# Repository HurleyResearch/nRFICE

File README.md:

# nRFICE
### nRF5340 with ICE40UP5K including JLink OB for instant BLE and FPGA development with zero dongles
In order to develop a number of comercial products, we (here at Hurley Research in Santa Cruz CA) needed a simple bluetooth 5 plus FPGA platform. nRFICE is meant to be a maximally simple solution for launching projects that require MCU plus FPGA and certainly if Bluetooth including mesh is needed.
### Arduino Uno compatibility
nRFICE is physically compatible with Arduino Uno shields, but take care that the GPIO level is 3.3V.
### JLink OB
Comercial eval/dev boards from chip manufactures, such as Nordic Semi, typically have the JLink debugger hardware embedded on the board for convenience. We have included JLink OB on nRFICE, allowing developers to get started without any additional hardare, programming dongles, etc. Out of box demos for both nRF5340 and ICE40UP5K can be loaded and debugged immediately with a single usb cable, or over BLE with the nRFICE android app.

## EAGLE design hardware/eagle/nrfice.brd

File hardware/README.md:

# nRFICE Hardware
Everything about the nRFICE PCB
- Eagle design files
- Gerbers
- Schematic
- Bill of matrials
- Pinout diagram

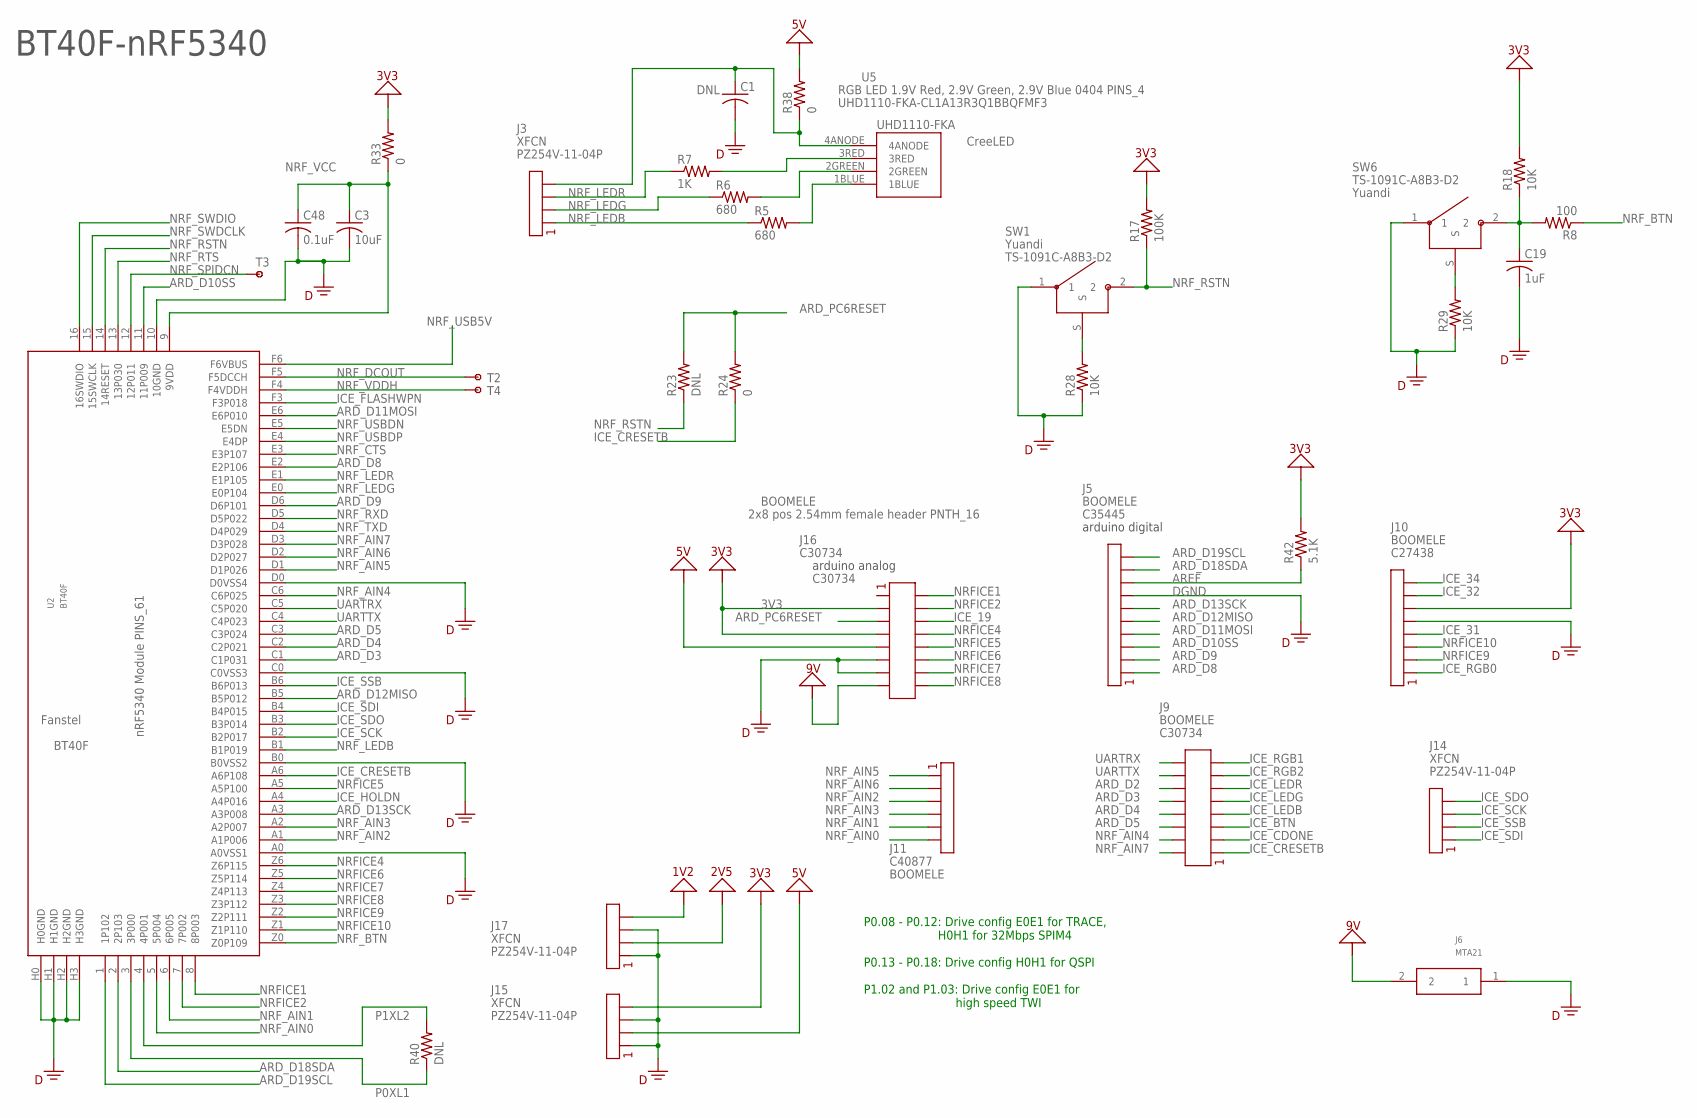
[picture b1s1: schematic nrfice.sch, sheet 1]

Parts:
C1: DNL; RCL_C0402; MPN CL05A105KP5NNNC
C3: 10uF; RCL_C0805; MPN CL21A106KOQNNNE
C19: 1uF; RCL_C0402; MPN CL05A105KP5NNNC
C48: 0.1uF; RCL_C0402; MPN C0402C104K8RAC7867
J3, J14, J15, J17: PZ254V-11-04P; MPN PZ254V-11-04P
J5: C35445; MPN C35445
J6: MTA21
J9, J16: C30734; MPN C30734
J10: C27438; MPN C27438
J11: C40877; MPN C40877
R5, R6: 680; RCL_R0402; MPN RC0402FR-07680RL
R7: 1K; RCL_R0402; MPN RC0402FR-071KL
R8: 100; RCL_R0402; MPN RC0402FR-07100RL
R17: 100K; RCL_R0402; MPN RC0402FR-07100KL
R18, R28, R29: 10K; RCL_R0402; MPN RC0402FR-0710KL
R23, R40: DNL; RCL_R0402; MPN RC0402FR-0710KL
R24, R38: 0; RCL_R0402; MPN RC0402FR-070RL
R33: 0; RCL_R0603; MPN RC0603FR-070RL
R42: 5.1K; RCL_R0402; MPN RC0402FR-075K1L
SW1, SW6: TS-1091C-A8B3-D2; MPN TS-1091C-A8B3-D2
T2, T3, T4: MTA1
U2: BT40F; MPN BT40F
U5: UHD1110-FKA; MPN UHD1110-FKA-CL1A13R3Q1BBQFMF3

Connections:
1V2: J17.4; also elsewhere on the board
2V5: J17.2; also elsewhere on the board
3V3: J10.6, J15.4, J16.3, J16.7, R17.2, R18.2, R33.2, R42.2; also elsewhere on the board
5V: J15.2, J16.9, R38.2; also elsewhere on the board
9V: J6.2, J16.15; also elsewhere on the board
ARD_D2: J9.12; also elsewhere on the board
ARD_D3: J9.10, U2.C1 (C1P031); also elsewhere on the board
ARD_D4: J9.8, U2.C2 (C2P021); also elsewhere on the board
ARD_D5: J9.6, U2.C3 (C3P024); also elsewhere on the board
ARD_D8: J5.1, U2.E2 (E2P106); also elsewhere on the board
ARD_D9: J5.2, U2.D6 (D6P101); also elsewhere on the board
ARD_D10SS: J5.3, U2.11 (11P009); also elsewhere on the board
ARD_D11MOSI: J5.4, U2.E6 (E6P010); also elsewhere on the board
ARD_D12MISO: J5.5, U2.B5 (B5P012); also elsewhere on the board
ARD_D13SCK: J5.6, U2.A3 (A3P008); also elsewhere on the board
ARD_D18SDA: J5.9, U2.2 (2P103); also elsewhere on the board
ARD_D19SCL: J5.10, U2.1 (1P102); also elsewhere on the board
ARD_PC6RESET: J16.5, R23.2, R24.2
AREF: J5.8, R42.1
DGND: C1.2, C3.2, C19.2, C48.2, J5.7, J6.1, J10.5, J15.1, J15.3, J16.11, J16.13, J17.1, J17.3, R28.1, R29.1, SW1.1, SW6.1, U2.10 (10GND), U2.A0 (A0VSS1), U2.B0 (B0VSS2), U2.C0 (C0VSS3), U2.D0 (D0VSS4), U2.H0 (H0GND), U2.H1 (H1GND), U2.H2 (H2GND), U2.H3 (H3GND); also elsewhere on the board
ICE_19: J16.6; also elsewhere on the board
ICE_31: J10.4; also elsewhere on the board
ICE_32: J10.7; also elsewhere on the board
ICE_34: J10.8; also elsewhere on the board
ICE_BTN: J9.5; also elsewhere on the board
ICE_CDONE: J9.3; also elsewhere on the board
ICE_CRESETB: J9.1, R24.1, U2.A6 (A6P108); also elsewhere on the board
ICE_FLASHWPN: U2.F3 (F3P018); also elsewhere on the board
ICE_HOLDN: U2.A4 (A4P016); also elsewhere on the board
ICE_LEDB: J9.7; also elsewhere on the board
ICE_LEDG: J9.9; also elsewhere on the board
ICE_LEDR: J9.11; also elsewhere on the board
ICE_RGB0: J10.1; also elsewhere on the board
ICE_RGB1: J9.15; also elsewhere on the board
ICE_RGB2: J9.13; also elsewhere on the board
ICE_SCK: J14.3, U2.B2 (B2P017); also elsewhere on the board
ICE_SDI: J14.1, U2.B4 (B4P015); also elsewhere on the board
ICE_SDO: J14.4, U2.B3 (B3P014); also elsewhere on the board
ICE_SSB: J14.2, U2.B6 (B6P013); also elsewhere on the board
unnamed: R5.2, U5.1BLUE
unnamed: R6.2, U5.2GREEN
unnamed: R7.2, U5.3RED
unnamed: C19.1, R8.2, R18.1, SW6.2
unnamed: R28.2, SW1.S
unnamed: R29.2, SW6.S
unnamed: C1.1, J3.4, R38.1, U5.4ANODE
NRFICE1: J16.2, U2.8 (8P003); also elsewhere on the board
NRFICE2: J16.4, U2.7 (7P002); also elsewhere on the board
NRFICE4: J16.8, U2.Z6 (Z6P115); also elsewhere on the board
NRFICE5: J16.10, U2.A5 (A5P100); also elsewhere on the board
NRFICE6: J16.12, U2.Z5 (Z5P114); also elsewhere on the board
NRFICE7: J16.14, U2.Z4 (Z4P113); also elsewhere on the board
NRFICE8: J16.16, U2.Z3 (Z3P112); also elsewhere on the board
NRFICE9: J10.2, U2.Z2 (Z2P111); also elsewhere on the board
NRFICE10: J10.3, U2.Z1 (Z1P110); also elsewhere on the board
NRF_AIN0: J11.6, U2.5 (5P004)
NRF_AIN1: J11.5, U2.6 (6P005)
NRF_AIN2: J11.3, U2.A1 (A1P006)
NRF_AIN3: J11.4, U2.A2 (A2P007)
NRF_AIN4: J9.4, U2.C6 (C6P025)
NRF_AIN5: J11.1, U2.D1 (D1P026)
NRF_AIN6: J11.2, U2.D2 (D2P027)
NRF_AIN7: J9.2, U2.D3 (D3P028)
NRF_BTN: R8.1, U2.Z0 (Z0P109)
NRF_CTS: U2.E3 (E3P107); also elsewhere on the board
NRF_DCOUT: T2.1, U2.F5 (F5DCCH)
NRF_LEDB: J3.1, R5.1, U2.B1 (B1P019)
NRF_LEDG: J3.2, R6.1, U2.E0 (E0P104)
NRF_LEDR: J3.3, R7.1, U2.E1 (E1P105)
NRF_RSTN: R17.1, R23.1, SW1.2, U2.14 (14RESET); also elsewhere on the board
NRF_RTS: U2.13 (13P030); also elsewhere on the board
NRF_RXD: U2.D5 (D5P022); also elsewhere on the board
NRF_SPIDCN: T3.1, U2.12 (12P011)
NRF_SWDCLK: U2.15 (15SWCLK); also elsewhere on the board
NRF_SWDIO: U2.16 (16SWDIO); also elsewhere on the board
NRF_TXD: U2.D4 (D4P029); also elsewhere on the board
NRF_USB5V: U2.F6 (F6VBUS); also elsewhere on the board
NRF_USBDN: U2.E5 (E5DN); also elsewhere on the board
NRF_USBDP: U2.E4 (E4DP); also elsewhere on the board
NRF_VCC: C3.1, C48.1, R33.1, U2.9 (9VDD)
NRF_VDDH: T4.1, U2.F4 (F4VDDH)
P0XL1: R40.1, U2.3 (3P000)
P1XL2: R40.2, U2.4 (4P001)
UARTRX: J9.16, U2.C5 (C5P020); also elsewhere on the board
UARTTX: J9.14, U2.C4 (C4P023); also elsewhere on the board

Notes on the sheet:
BT40F-nRF5340
arduino analog
arduino digital
P0.08 - P0.12: Drive config E0E1 for TRACE, H0H1 for 32Mbps SPIM4 P0.13 - P0.18: Drive config H0H1 for QSPI P1.02 and P1.03: Drive config E0E1 for high speed TWI

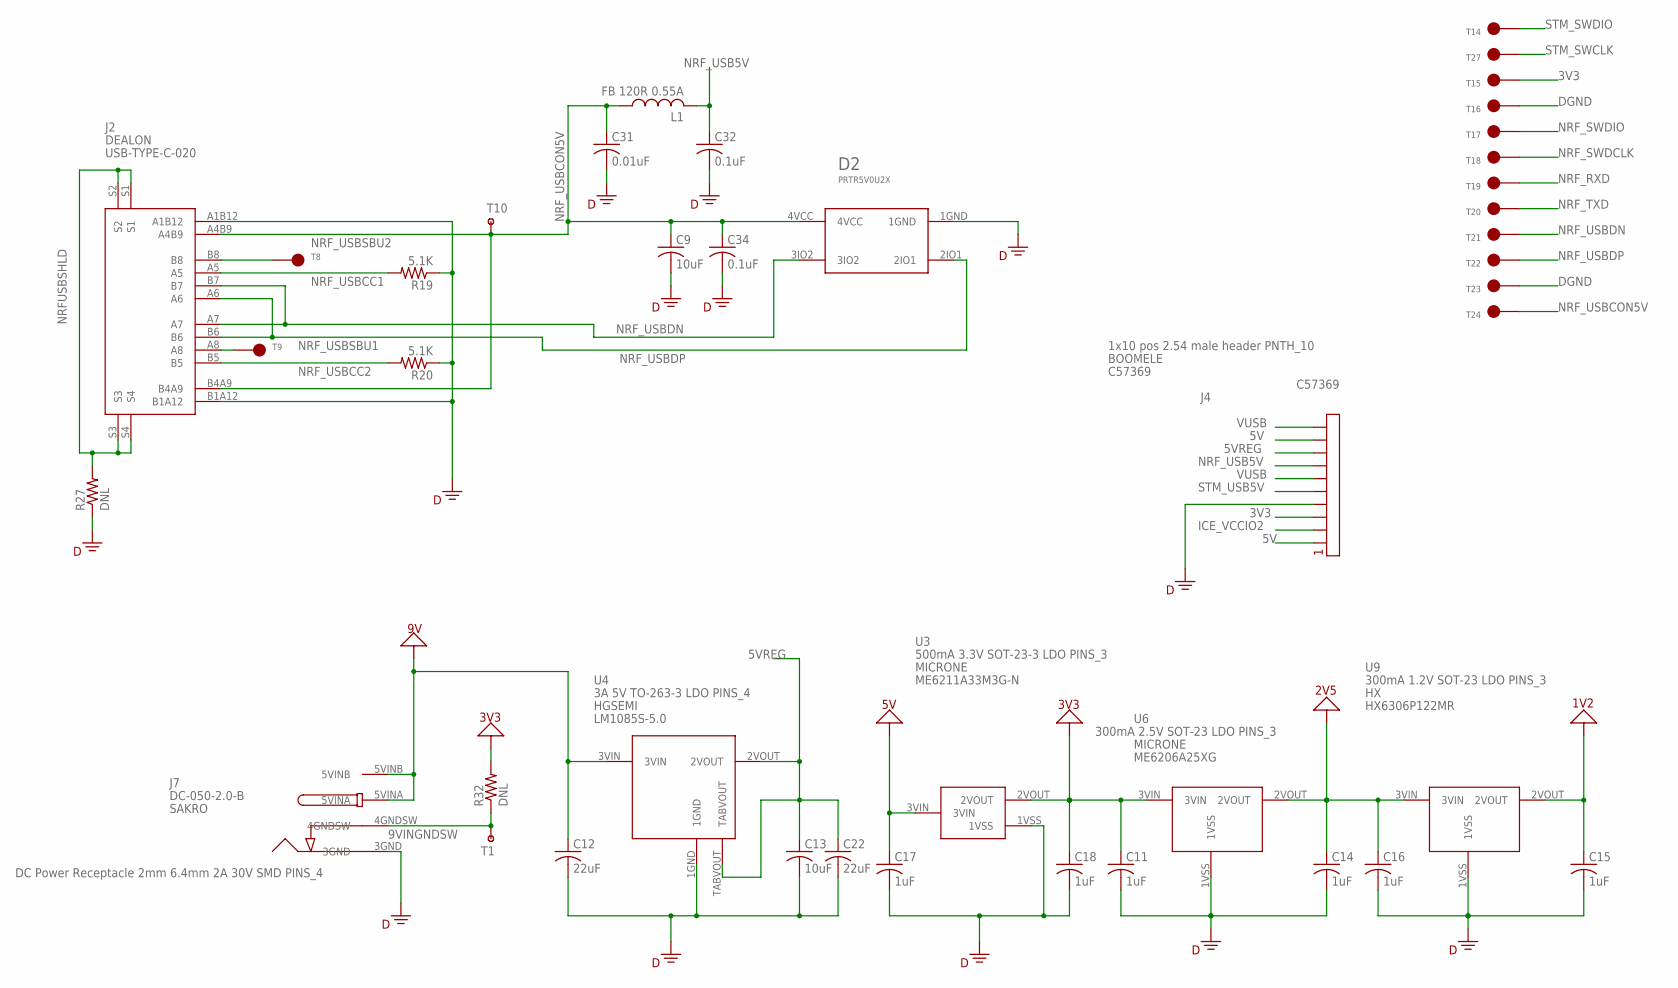
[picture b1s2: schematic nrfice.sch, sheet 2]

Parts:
C9, C13: 10uF; RCL_C0805; MPN CL21A106KOQNNNE
C11, C14, C15, C16, C17, C18: 1uF; RCL_C0402; MPN CL05A105KP5NNNC
C12, C22: 22uF; RCL_C0805; MPN CL21A226MAYNNNE
C31: 0.01uF; RCL_C0402; MPN C0402C103J4RAC
C32, C34: 0.1uF; RCL_C0402; MPN C0402C104K8RAC7867
D2: PRTR5V0U2X; MPN PRTR5V0U2X
J2: USB-TYPE-C-020; MPN USB-TYPE-C-020
J4: C57369; MPN C57369
J7: DC-050-2.0-B; MPN DC-050-2.0-B
L1: FB 120R 0.55A; L0402; MPN BLM15AG121SN1D
R19, R20: 5.1K; RCL_R0402; MPN RC0402FR-075K1L
R27, R32: DNL; RCL_R0402; MPN RC0402FR-0710KL
T1, T10: MTA1
T8, T9: T
T14, T15, T16, T17, T18, T19, T20, T21, T22, T23, T24, T27: TT2; T2
U3: ME6211A33M3G-N; MPN ME6211A33M3G-N
U4: LM1085S-5.0; MPN LM1085S-5.0
U6: ME6206A25XG; MPN ME6206A25XG
U9: HX6306P122MR; MPN HX6306P122MR

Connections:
1V2: C15.1, U9.2VOUT; also elsewhere on the board
2V5: C14.1, C16.1, U6.2VOUT, U9.3VIN; also elsewhere on the board
3V3: C11.1, C18.1, J4.3, R32.2, T15.T, U3.2VOUT, U6.3VIN; also elsewhere on the board
5V: C17.1, J4.1, J4.9, U3.3VIN; also elsewhere on the board
5VREG: C13.1, C22.1, J4.8, U4.2VOUT, U4.TABVOUT
9V: C12.1, J7.5VINA, J7.5VINB, U4.3VIN; also elsewhere on the board
9VINGNDSW: J7.4GNDSW, R32.1, T1.1
DGND: C9.2, C11.2, C12.2, C13.2, C14.2, C15.2, C16.2, C17.2, C18.2, C22.2, C31.2, C32.2, C34.2, D2.1GND, J2.A1B12, J2.B1A12, J4.4, J7.3GND, R19.1, R20.1, R27.1, T16.T, T23.T, U3.1VSS, U4.1GND, U6.1VSS, U9.1VSS; also elsewhere on the board
ICE_VCCIO2: J4.2; also elsewhere on the board
NRFUSBSHLD: J2.S1, J2.S2, J2.S3, J2.S4, R27.2
NRF_RXD: T19.T; also elsewhere on the board
NRF_SWDCLK: T18.T; also elsewhere on the board
NRF_SWDIO: T17.T; also elsewhere on the board
NRF_TXD: T20.T; also elsewhere on the board
NRF_USB5V: C32.1, J4.7, L1.2; also elsewhere on the board
NRF_USBCC1: J2.A5, R19.2
NRF_USBCC2: J2.B5, R20.2
NRF_USBCON5V: C9.1, C31.1, C34.1, D2.4VCC, J2.A4B9, J2.B4A9, L1.1, T10.1, T24.T
NRF_USBDN: D2.3IO2, J2.A7, J2.B7, T21.T; also elsewhere on the board
NRF_USBDP: D2.2IO1, J2.A6, J2.B6, T22.T; also elsewhere on the board
NRF_USBSBU1: J2.A8, T9.T
NRF_USBSBU2: J2.B8, T8.T
STM_SWCLK: T27.T; also elsewhere on the board
STM_SWDIO: T14.T; also elsewhere on the board
STM_USB5V: J4.5; also elsewhere on the board
VUSB: J4.6, J4.10

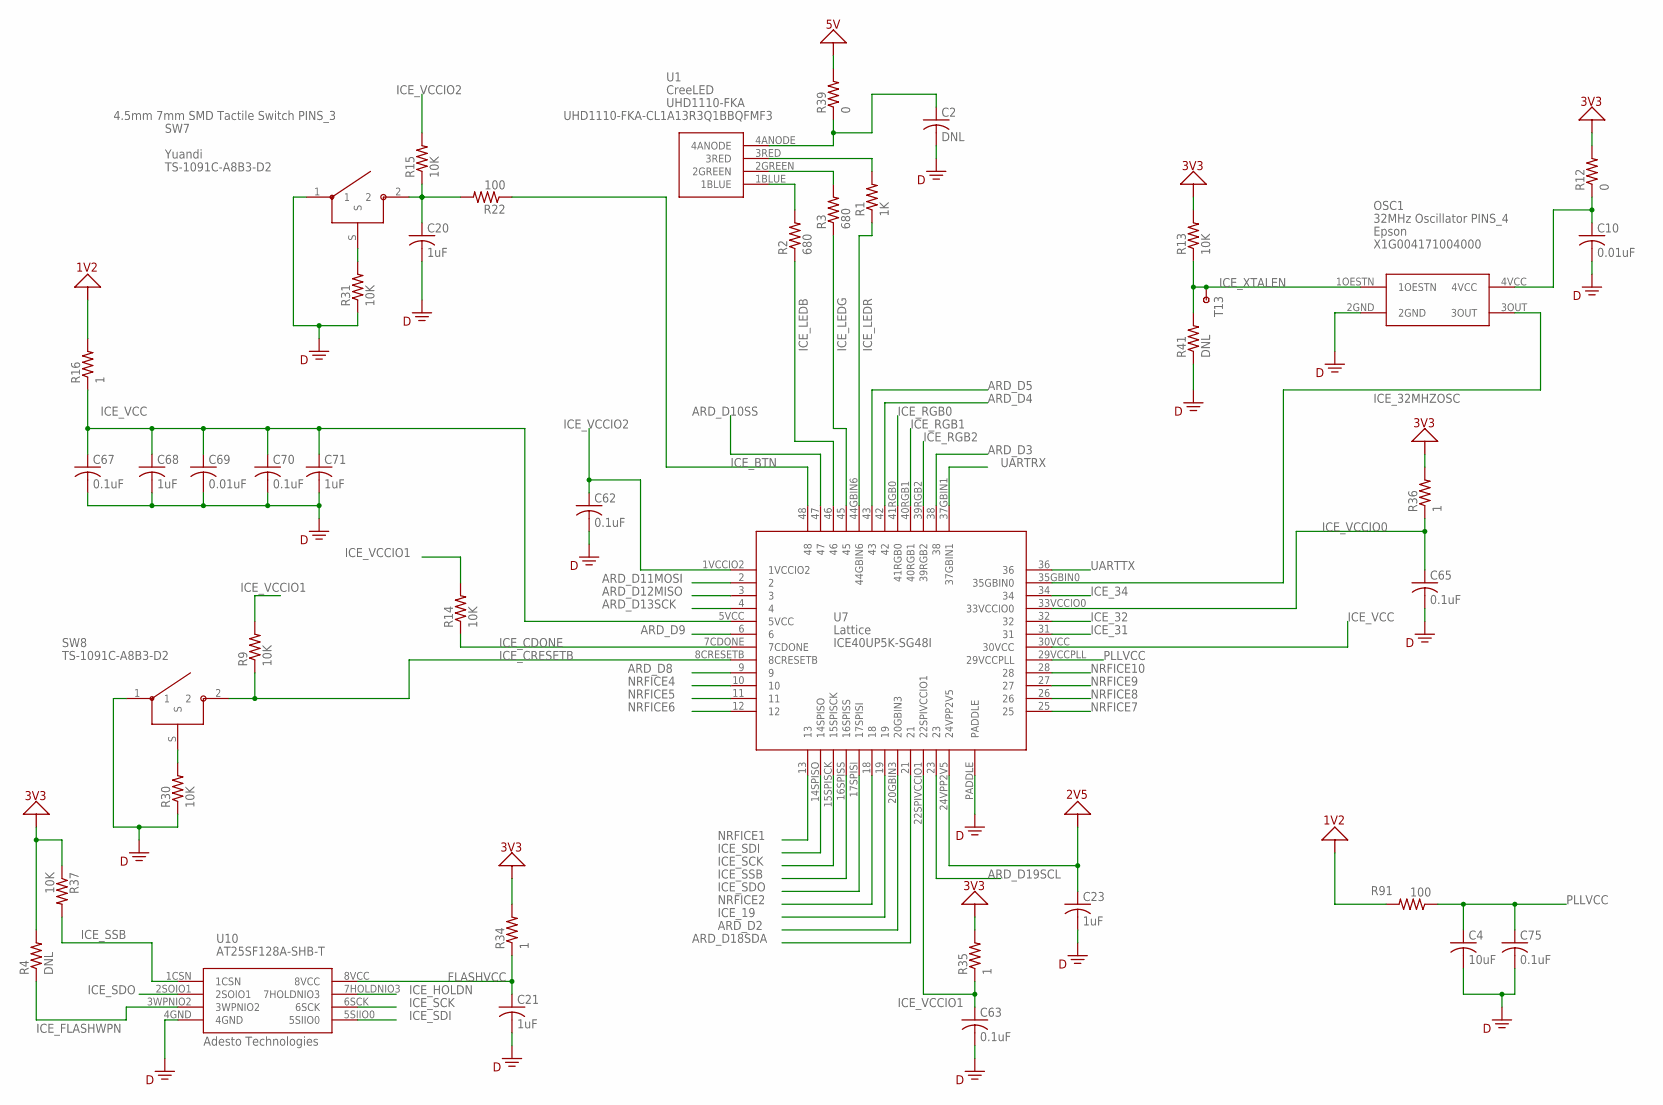
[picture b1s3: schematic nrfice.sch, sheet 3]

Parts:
C2: DNL; RCL_C0402; MPN CL05A105KP5NNNC
C4: 10uF; RCL_C0805; MPN CL21A106KOQNNNE
C10, C69: 0.01uF; RCL_C0402; MPN C0402C103J4RAC
C20, C21, C23, C68, C71: 1uF; RCL_C0402; MPN CL05A105KP5NNNC
C62, C63, C65, C67, C70, C75: 0.1uF; RCL_C0402; MPN C0402C104K8RAC7867
OSC1: X1G004171004000; MPN X1G004171004000
R1: 1K; RCL_R0402; MPN RC0402FR-071KL
R2, R3: 680; RCL_R0402; MPN RC0402FR-07680RL
R4, R41: DNL; RCL_R0402; MPN RC0402FR-0710KL
R9, R13, R14, R15, R30, R31, R37: 10K; RCL_R0402; MPN RC0402FR-0710KL
R12: 0; RCL_R0603; MPN RC0603FR-070RL
R16, R34, R35, R36: 1; RCL_R0603; MPN RC0603FR-071RL
R22, R91: 100; RCL_R0402; MPN RC0402FR-07100RL
R39: 0; RCL_R0402; MPN RC0402FR-070RL
SW7, SW8: TS-1091C-A8B3-D2; MPN TS-1091C-A8B3-D2
T13: MTA1
U1: UHD1110-FKA; MPN UHD1110-FKA-CL1A13R3Q1BBQFMF3
U7: ICE40UP5K-SG48I; MPN ICE40UP5K-SG48I
U10: AT25SF128A-SHB-T; MPN AT25SF128A-SHB-T

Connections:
1V2: R16.2, R91.2; also elsewhere on the board
2V5: C23.1, U7.24VPP2V5; also elsewhere on the board
3V3: R4.2, R12.2, R13.2, R34.2, R35.2, R36.2, R37.1; also elsewhere on the board
5V: R39.2; also elsewhere on the board
ARD_D2: U7.20GBIN3; also elsewhere on the board
ARD_D3: U7.38; also elsewhere on the board
ARD_D4: U7.42; also elsewhere on the board
ARD_D5: U7.43; also elsewhere on the board
ARD_D8: U7.9; also elsewhere on the board
ARD_D9: U7.6; also elsewhere on the board
ARD_D10SS: U7.47; also elsewhere on the board
ARD_D11MOSI: U7.2; also elsewhere on the board
ARD_D12MISO: U7.3; also elsewhere on the board
ARD_D13SCK: U7.4; also elsewhere on the board
ARD_D18SDA: U7.21; also elsewhere on the board
ARD_D19SCL: U7.23; also elsewhere on the board
DGND: C2.2, C4.2, C10.2, C20.2, C21.2, C23.2, C62.2, C63.2, C65.2, C67.2, C68.2, C69.2, C70.2, C71.2, C75.2, OSC1.2GND, R30.1, R31.1, R41.1, SW7.1, SW8.1, U7.PADDLE, U10.4GND; also elsewhere on the board
FLASHVCC: C21.1, R34.1, U10.8VCC
ICE_19: U7.19; also elsewhere on the board
ICE_31: U7.31; also elsewhere on the board
ICE_32: U7.32; also elsewhere on the board
ICE_32MHZOSC: OSC1.3OUT, U7.35GBIN0
ICE_34: U7.34; also elsewhere on the board
ICE_BTN: R22.1, U7.48; also elsewhere on the board
ICE_CDONE: R14.1, U7.7CDONE; also elsewhere on the board
ICE_CRESETB: R9.1, SW8.2, U7.8CRESETB; also elsewhere on the board
ICE_FLASHWPN: R4.1, U10.3WPNIO2; also elsewhere on the board
ICE_HOLDN: U10.7HOLDNIO3; also elsewhere on the board
ICE_LEDB: R2.1, U7.46; also elsewhere on the board
ICE_LEDG: R3.1, U7.45; also elsewhere on the board
ICE_LEDR: R1.1, U7.44GBIN6; also elsewhere on the board
ICE_RGB0: U7.41RGB0; also elsewhere on the board
ICE_RGB1: U7.40RGB1; also elsewhere on the board
ICE_RGB2: U7.39RGB2; also elsewhere on the board
ICE_SCK: U7.15SPISCK, U10.6SCK; also elsewhere on the board
ICE_SDI: U7.14SPISO, U10.5SIIO0; also elsewhere on the board
ICE_SDO: U7.17SPISI, U10.2SOIO1; also elsewhere on the board
ICE_SSB: R37.2, U7.16SPISS, U10.1CSN; also elsewhere on the board
ICE_VCC: C67.1, C68.1, C69.1, C70.1, C71.1, R16.1, U7.5VCC, U7.30VCC
ICE_VCCIO0: C65.1, R36.1, U7.33VCCIO0
ICE_VCCIO1: C63.1, R9.2, R14.2, R35.1, U7.22SPIVCCIO1
ICE_VCCIO2: C62.1, R15.2, U7.1VCCIO2; also elsewhere on the board
ICE_XTALEN: OSC1.1OESTN, R13.1, R41.2, T13.1
unnamed: R1.2, U1.3RED
unnamed: R3.2, U1.2GREEN
unnamed: R2.2, U1.1BLUE
unnamed: C10.1, OSC1.4VCC, R12.1
unnamed: C20.1, R15.1, R22.2, SW7.2
unnamed: R31.2, SW7.S
unnamed: R30.2, SW8.S
unnamed: C2.1, R39.1, U1.4ANODE
NRFICE1: U7.13; also elsewhere on the board
NRFICE2: U7.18; also elsewhere on the board
NRFICE4: U7.10; also elsewhere on the board
NRFICE5: U7.11; also elsewhere on the board
NRFICE6: U7.12; also elsewhere on the board
NRFICE7: U7.25; also elsewhere on the board
NRFICE8: U7.26; also elsewhere on the board
NRFICE9: U7.27; also elsewhere on the board
NRFICE10: U7.28; also elsewhere on the board
PLLVCC: C4.1, C75.1, R91.1, U7.29VCCPLL
UARTRX: U7.37GBIN1; also elsewhere on the board
UARTTX: U7.36; also elsewhere on the board

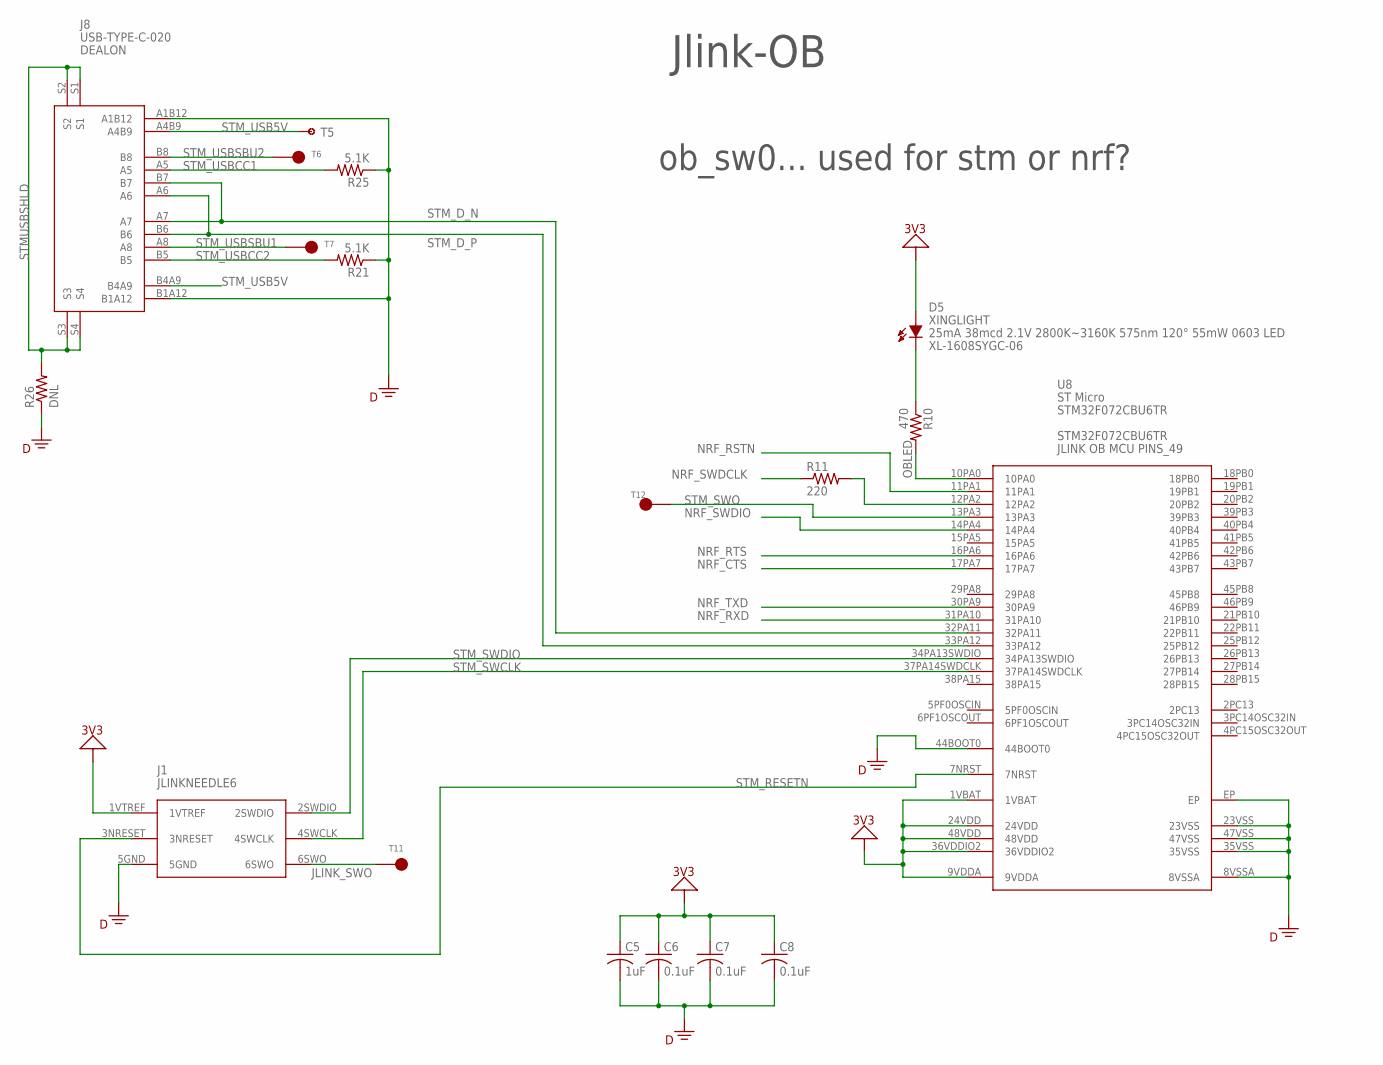
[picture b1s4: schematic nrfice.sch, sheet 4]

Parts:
C5: 1uF; RCL_C0402; MPN CL05A105KP5NNNC
C6, C7, C8: 0.1uF; RCL_C0402; MPN C0402C104K8RAC7867
D5: XL-1608SYGC-06; MPN XL-1608SYGC-06
J1: JLINKNEEDLE6
J8: USB-TYPE-C-020; MPN USB-TYPE-C-020
R10: 470; RCL_R0402; MPN RC0402FR-07470RL
R11: 220; RCL_R0402; MPN RC0402FR-07220RL
R21, R25: 5.1K; RCL_R0402; MPN RC0402FR-075K1L
R26: DNL; RCL_R0402; MPN RC0402FR-0710KL
T5: MTA1
T6, T7, T11, T12: T
U8: STM32F072CBU6TR; MPN STM32F072CBU6TR

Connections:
3V3: C5.1, C6.1, C7.1, C8.1, D5.A, J1.1VTREF, U8.1VBAT, U8.9VDDA, U8.24VDD, U8.36VDDIO2, U8.48VDD; also elsewhere on the board
DGND: C5.2, C6.2, C7.2, C8.2, J1.5GND, J8.A1B12, J8.B1A12, R21.1, R25.1, R26.1, U8.8VSSA, U8.23VSS, U8.35VSS, U8.44BOOT0, U8.47VSS, U8.EP; also elsewhere on the board
JLINK_SWO: J1.6SWO, T11.T
unnamed: R11.2, U8.12PA2
unnamed: D5.C, R10.1
NRF_CTS: U8.17PA7; also elsewhere on the board
NRF_RSTN: U8.11PA1; also elsewhere on the board
NRF_RTS: U8.16PA6; also elsewhere on the board
NRF_RXD: U8.31PA10; also elsewhere on the board
NRF_SWDCLK: R11.1; also elsewhere on the board
NRF_SWDIO: U8.14PA4; also elsewhere on the board
NRF_TXD: U8.30PA9; also elsewhere on the board
OBLED: R10.2, U8.10PA0
STMUSBSHLD: J8.S1, J8.S2, J8.S3, J8.S4, R26.2
STM_D_N: J8.A7, J8.B7, U8.32PA11
STM_D_P: J8.A6, J8.B6, U8.33PA12
STM_RESETN: J1.3NRESET, U8.7NRST
STM_SWCLK: J1.4SWCLK, U8.37PA14SWDCLK; also elsewhere on the board
STM_SWDIO: J1.2SWDIO, U8.34PA13SWDIO; also elsewhere on the board
STM_SWO: T12.T, U8.13PA3
STM_USB5V: J8.A4B9, J8.B4A9, T5.1; also elsewhere on the board
STM_USBCC1: J8.A5, R25.2
STM_USBCC2: J8.B5, R21.2
STM_USBSBU1: J8.A8, T7.T
STM_USBSBU2: J8.B8, T6.T

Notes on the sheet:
Jlink-OB
ob_sw0... used for stm or nrf?

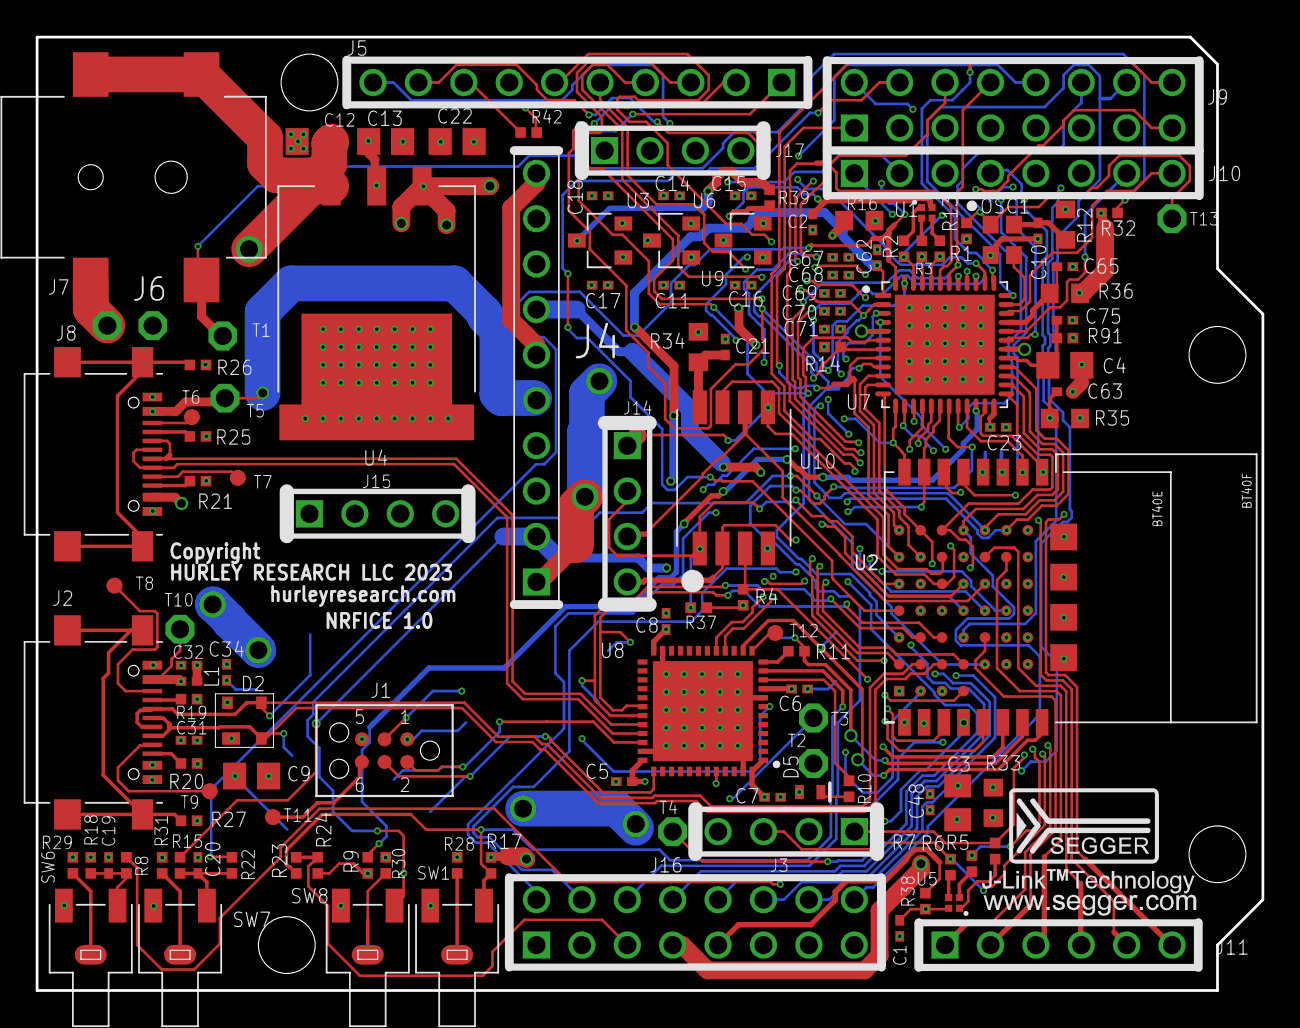
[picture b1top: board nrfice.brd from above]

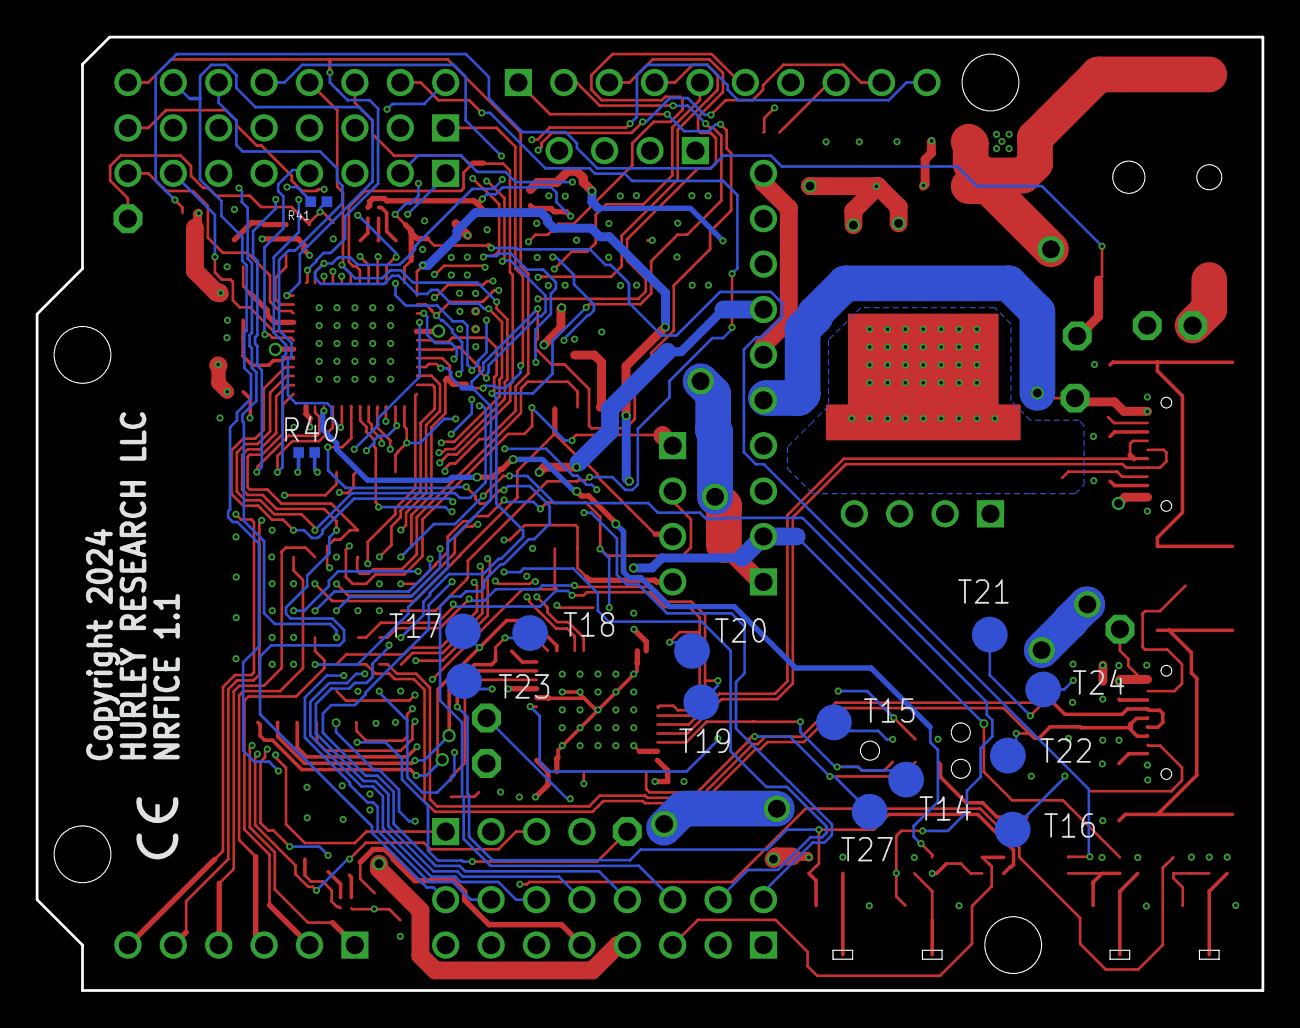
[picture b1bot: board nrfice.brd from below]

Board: 4 copper layers, 68.6 x 53.3 mm, 137 parts (14 on the bottom side), 126 nets.

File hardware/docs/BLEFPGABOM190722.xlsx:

Manufacturer | Manufacturer Part Number | Designator | Quantity | Description | Case | SMD BGA LLC(QFN) TH | Top/Bottom | points | Total points
BOOMELE | C30734 | J16, J9 | 2.0 | 2x8 pos 2.54mm female header | C30734 | TH | Top | 16.0 | 32.0
Adesto Technologies | AT25SF128A-SHB-T | U10 | 1.0 | NOR Flash 128 Mbit,2.7V to 3.6V,SOIC-W 208mil | AT25SF128A-SHB-T | SMD | Top | 8.0 | 8.0
BOOMELE | C40877 | J11 | 1.0 | 1x6 pos 2.54 female header | C40877 | TH | Top | 6.0 | 6.0
YAGEO | RC0402FR-075K1L | R19, R20, R21, R25 | 4.0 | 5.1K,1%,1/16W,0402 | RCL_R0402 | SMD | Top | 2.0 | 8.0
MICRONE | ME6211A33M3G-N | U3 | 1.0 | 500mA 3.3V SOT-23-3 LDO | ME6211A33M3G-N | SMD | Top | 3.0 | 3.0
MICRONE | ME6206A25XG | U6 | 1.0 | 300mA 2.5V SOT-23 LDO | ME6206A25XG | SMD | Top | 3.0 | 3.0
Samsung | CL05A105KP5NNNC | C11, C14, C15, C16, C17, C18, C19, C20, C21, C23, C5, C68, C71 | 13.0 | 1uF,10V,10%,X5R,0402 | RCL_C0402 | SMD | Top | 2.0 | 26.0
YAGEO | RC0402FR-07100RL | R22, R8, R91 | 3.0 | 100 Ohm,1%,1/16W,0402 | RCL_R0402 | SMD | Top | 2.0 | 6.0
YAGEO | RC0402FR-07220RL | R11 | 1.0 | 220 Ohm,1%,1/16W,0402 | RCL_R0402 | SMD | Top | 2.0 | 2.0
YAGEO | RC0402FR-070RL | R24, R38, R39 | 3.0 | 0 Ohm,1%,1/16W,0402 | RCL_R0402 | SMD | Top | 2.0 | 6.0
Murata | BLM15AG121SN1D | L1 | 1.0 | FERRITE BEAD 120 OHM 0402 1LN | L0402 | SMD | Top | 2.0 | 2.0
ST Micro | STM32F072CBU6TR | U8 | 1.0 | JLINK OB MCU | STM32F072CBU6TR | SMD | Top | 49.0 | 49.0
XFCN | PZ254V-11-04P | J14, J15, J17, J3 | 4.0 | 1x4 pos 2.54 male header | PZ254V-11-04P | TH | Top | 4.0 | 16.0
BOOMELE | C35445 | J5 | 1.0 | 1x10 pos 2.54 female header | C35445 | TH | Top | 10.0 | 10.0
Fanstel | BT40F | U2 | 1.0 | nRF5340 Module | BT40F | SMD | Top | 61.0 | 61.0
YAGEO | RC0402FR-07100KL | R17 | 1.0 | 100K Ohm,1%,1/16W,0402 | RCL_R0402 | SMD | Top | 2.0 | 2.0
YAGEO | RC0402FR-07470RL | R10 | 1.0 | 470 Ohm,1%,1/16W,0402 | RCL_R0402 | SMD | Top | 2.0 | 2.0
YAGEO | RC0402FR-0710KL | R13, R14, R15, R18, R26, R27, R28, R29, R30, R31, R32, R37, R9 | 13.0 | 10K Ohm,1%,1/16W,0402 | RCL_R0402 | SMD | Top | 2.0 | 26.0
HX | HX6306P122MR | U9 | 1.0 | 300mA 1.2V SOT-23 LDO | HX6306P122MR | SMD | Top | 3.0 | 3.0
HGSEMI | LM1085S-5.0 | U4 | 1.0 | 3A 5V TO-263-3 LDO | LM1085S-5.0 | SMD | Top | 4.0 | 4.0
Yuandi | TS-1091C-A8B3-D2 | S1, S6, S7, S8 | 4.0 | 4.5mm 7mm SMD Tactile Switch | TS-1091C-A8B3-D2 | SMD | Top | 3.0 | 12.0
Samsung | CL21A106KOQNNNE | C12, C13, C3, C4, C9 | 5.0 | 10uF,16V,10%,X5R,0805 | RCL_C0805 | SMD | Top | 2.0 | 10.0
YAGEO | RC0402FR-071KL | R1, R5 | 2.0 | 1K Ohm,1%,1/16W,0402 | RCL_R0402 | SMD | Top | 2.0 | 4.0
SAKRO | DC-050-2.0-B | J7 | 1.0 | DC Power Receptacle 2mm 6.4mm 2A 30V SMD | DC-050-2.0-B | SMD | Top | 4.0 | 4.0
KEMET | C0402C104K8RAC7867 | C32, C34, C48, C6, C62, C63, C65, C67, C7, C70, C75, C8 | 12.0 | 0.1uF,10V,10%,X7R,0402 | RCL_C0402 | SMD | Top | 2.0 | 24.0
BOOMELE | C57369 | J4 | 1.0 | 1x10 pos 2.54 male header | C57369 | TH | Top | 10.0 | 10.0
YAGEO | RC0402FR-07680RL | R2, R3, R6, R7 | 4.0 | 680 Ohms,1%,1/16W,0402 | RCL_R0402 | SMD | Top | 2.0 | 8.0
Samsung | CL21A226MAYNNNE | C22 | 1.0 | 22uF,25V,20%,X5R,0805 | RCL_C0805 | SMD | Top | 2.0 | 2.0
XINGLIGHT | XL-1608SYGC-06 | D5 | 1.0 | 25mA 38mcd 2.1V 2800K~3160K 575nm 120° 55mW 0603 LED | XL-1608SYGC-06 | SMD | Top | 2.0 | 2.0
Nexperia | PRTR5V0U2X | D2 | 1.0 | TVS DIODE 5.5VWM SOT143B | PRTR5V0U2X | SMD | Top | 4.0 | 4.0
DEALON | USB-TYPE-C-020 | J2, J8 | 2.0 | usb type c connector | USB-TYPE-C-020 | SMD | Top | 12.0 | 24.0
CreeLED | UHD1110-FKA-CL1A13R3Q1BBQFMF3 | U1, U5 | 2.0 | RGB LED 1.9V Red, 2.9V Green, 2.9V Blue 0404 | UHD1110-FKA | SMD | Top | 4.0 | 8.0
YAGEO | RC0603FR-071RL | R16, R34, R35, R36 | 4.0 | 1 Ohm,1%,1/10W,0603 | RCL_R0603 | SMD | Top | 2.0 | 8.0
KEMET | C0402C103J4RAC | C10, C31, C69 | 3.0 | 0.01uF,16V,5%,X7R,0402 | RCL_C0402 | SMD | Top | 2.0 | 6.0
Lattice | ICE40UP5K-SG48I | U7 | 1.0 | FPGA 48-VFQFN | ICE40UP5K-SG48I | SMD | Top | 48.0 | 48.0
YAGEO | RC0603FR-070RL | R12, R33 | 2.0 | 0 Ohm,1%,1/10W,0603 | RCL_R0603 | SMD | Top | 2.0 | 4.0
Epson | X1G004171004000 | OSC1 | 1.0 | 32MHz Oscillator | X1G004171004000 | SMD | Top | 4.0 | 4.0

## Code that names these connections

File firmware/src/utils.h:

/*
MIT License

Copyright (c) 2024 Hurley Research LLC

Permission is hereby granted, free of charge, to any person obtaining a copy
of this software and associated documentation files (the "Software"), to deal
in the Software without restriction, including without limitation the rights
to use, copy, modify, merge, publish, distribute, sublicense, and/or sell
copies of the Software, and to permit persons to whom the Software is
furnished to do so, subject to the following conditions:

The above copyright notice and this permission notice shall be included in all
copies or substantial portions of the Software.

THE SOFTWARE IS PROVIDED "AS IS", WITHOUT WARRANTY OF ANY KIND, EXPRESS OR
IMPLIED, INCLUDING BUT NOT LIMITED TO THE WARRANTIES OF MERCHANTABILITY,
FITNESS FOR A PARTICULAR PURPOSE AND NONINFRINGEMENT. IN NO EVENT SHALL THE
AUTHORS OR COPYRIGHT HOLDERS BE LIABLE FOR ANY CLAIM, DAMAGES OR OTHER
LIABILITY, WHETHER IN AN ACTION OF CONTRACT, TORT OR OTHERWISE, ARISING FROM,
OUT OF OR IN CONNECTION WITH THE SOFTWARE OR THE USE OR OTHER DEALINGS IN THE
SOFTWARE.
 */

#ifndef UTILS
#define UTILS
#include <stdint.h>
//#include "skibtools.h"
#include "nrf5340_application.h"
#include "nrf5340_application_bitfields.h"

#define COMMSPACKETSIZE 128

#define IOINPUT 0
#define IOOUTPUT 1
#define ICCONNECT 0
#define ICDISCONNECT 1
#define PULLNOPULL 0
#define PULLDOWN 1
#define PULLUP 3
#define DRIVES0S1 0
#define DRIVEH0S1 1
#define DRIVES0H1 2
#define DRIVEH0H1 3
#define DRIVED0S1 4
#define DRIVED0H1 5
#define DRIVES0D1 6
#define DRIVEH0D1 7
#define DRIVEE0E1 11
#define SENSEDISABLE 0
#define SENSEHIGH 2
#define SENSELOW 3
#define MCUSELAPP 0
#define MCUSELNET 1
#define MCUSELPER 3
#define MCUSELTND 7
extern uint8_t randomByteIndex;

void indicate(uint8_t ledPin);

void pack32(uint32_t x, uint8_t data[], uint32_t loc);
void pack24(uint32_t x, uint8_t data[], uint32_t loc);
uint32_t unpack32(uint8_t data[], uint32_t loc);
uint16_t unpack16(uint8_t data[], uint32_t loc);
int32_t unpack24(uint8_t data[], uint32_t loc);
void packFloat(float x, uint8_t * data, uint32_t loc);
uint8_t randomByte(void);
float randomFloat(float lessThan);
uint8_t randomUInt8(uint8_t lessThan);
void pack16(uint16_t val,uint8_t * array, uint32_t index );

float unpackFloat( uint8_t source[], uint32_t loc );
void setupSeggerUART(void);

void lgv(char msg[], uint8_t val);
void lg(char msg[]);



uint32_t randomUInt32(void);
/////////////////////////////////// gpio
void pinClear(uint8_t pin);

void pinSet(uint8_t pin);

void gpioConfigOutput(uint32_t pn);

void gpioConfigOutputClear(uint32_t pn);

void gpioConfigOutputSet(uint32_t pn);

void gpioConfigInputNoPull(uint32_t pn);


uint8_t gpioPinRead(uint32_t pn);
void gpioConfigInputDisconnect(uint32_t pn);

void gpioConfigGeneral(uint8_t pn,uint8_t io, uint8_t inputConnect, uint8_t pull, uint8_t drive, uint8_t sense, uint8_t mcusel);

void gpioConfigOutputDrive(uint8_t pn, uint8_t drive) ;
void gpioConfigInput(uint8_t pn, uint8_t pull) ;

void gpioConfigInputPullUp(uint32_t pn);
void gpioConfigInputPullDown(uint32_t pn);





#define	ARD_D10SS	9
#define	ARD_D11MOSI	10
#define	ARD_D12MISO	12
#define	ARD_D13SCK	8
#define	ARD_D18SDA	35
#define	ARD_D19SCL	34
// #define	ARD_D2	24
#define	ARD_D3	31
#define	ARD_D4	21
#define	ARD_D5	24
#define	ARD_D8	38
#define	ARD_D9	33
#define	ICE_CRESETB	40
#define	ICE_FLASHWPN	18
#define	ICE_HOLDN	16
#define	ICE_SCK	17
#define	ICE_SDI	15
#define	ICE_SDO	14
#define	ICE_SSB	13
#define	NRFICE1	3
#define	NRFICE10	42
#define	NRF_BTN	41
#define	NRFICE2	2
//#define	NRFICE3	1
#define	NRFICE4	47
#define	NRFICE5	32
#define	NRFICE6	46
#define	NRFICE7	45
#define	NRFICE8	44
#define	NRFICE9	43
#define	NRF_AIN0	4
#define	NRF_AIN1	5
#define	NRF_AIN2	6
#define	NRF_AIN3	7
#define	NRF_AIN4	25
#define	NRF_AIN5	26
#define	NRF_AIN6	27
#define	NRF_AIN7	28

#define	NRF_LEDB	19
#define	NRF_LEDG	36
#define	NRF_LEDR	37

#define	NRF_SPIDCN	11

#define	UARTRX	20
#define	UARTTX	23



#define	NRF_RTS	39
#define	NRF_CTS	30
#define	NRF_RXD	29
#define	NRF_TXD	22




#define ICEAPP_SPICSN  ARD_D8       // 38
#define ICEAPP_SPICLK  ARD_D10SS    //  9
#define ICEAPP_SPIMOSI  ARD_D12MISO // 12
#define ICEAPP_SPIMISO  ARD_D13SCK  //  8


#define ICESOFTRESET  NRFICE4       // 47

#endif // UTILS

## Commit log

2023-05-17 Initial project load to github
2024-05-08 update to gerber files to reflect the final design as shipped to the board house.
2024-07-12 Updates to the android app, cleaned up hardware files, and update to firmware.

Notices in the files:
hardware/eagle/nrfice.brd:
Copyright 2024
